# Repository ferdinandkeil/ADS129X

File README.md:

# ADS129X

Driver and sketches for the Texas Instruments **ADS1299-4 / ADS1299-6 / ADS1299** on a **Teensy 3.6, 4.0, or 4.1**, plus a Classic-Bluetooth sketch for the **original ESP32** (ESP32-WROOM-32E or ESP32-PICO, for example the Adafruit ESP32 Feather V2).

The photographed carrier is a Teensy 4.0 stacked on an **ADS1299-6**. The firmware reads the ID register and uses that channel count. If the ID does not look like an ADS1299, it assumes **6 channels**. Host output is still an **8-channel OpenBCI packet**; channels the chip does not have are zero.

This follows the ADS1299 datasheet (SBAS499C), not the ADS1298 ECG defaults. There is no respiration, pace, or Wilson-terminal register. Address `0x15` is `MISC1` (SRB1). Bias is `BIAS_SENSP` / `BIAS_SENSN`.

## Wiring

SPI is **mode 1** (CPOL = 0, CPHA = 1), MSB first. SCLK is requested at **8 MHz** (the part allows 20 MHz at DVDD >= 2.7 V). `MOSI` drives ADS1299 `DIN`. `MISO` reads `DOUT`.

Tie `CLKSEL` high for the internal 2.048 MHz oscillator, and tie `DAISY_IN` to DGND when this is the only device. `PWDN` and `RESET` are active low. Hold `START` low until the sketch starts conversions. DRDY falls when a new frame is ready; the interrupt is falling-edge.

Analog supplies, the bias resistor network, and SRB1/BIASOUT wiring are on the carrier. The firmware turns the internal 4.5 V reference and the bias amplifier on; it does not create that analog network.

### Teensy 3.6, 4.0, and 4.1

These pins are the same on all three boards and match the stacked carrier used by `Serial_OBCI` (DRDY on 2, PWDN on 3, RESET on 5, START on 6, CS on 10). An earlier loose prototype used a different map (PWDN 2, RESET 3, START 4, DRDY 5, CS 10). Confirm the silk before flashing that older board. Override a pin with `-DADS1299_PIN_DRDY=5` (and the matching `ADS1299_PIN_*` names) or by editing the defaults in `ADS129X.h`.

| Teensy pin | ADS1299 pin | Notes |
| --- | --- | --- |
| 13 (SCK) | SCLK | Hardware SPI. Do not use the onboard LED; it shares this pin. |
| 11 (MOSI) | DIN | |
| 12 (MISO) | DOUT | |
| 10 | CS | Active low, GPIO, not the SPI peripheral's automatic CS. |
| 2 | DRDY | Falling-edge interrupt. |
| 6 | START | Held low during setup, then driven high. |
| 5 | RESET | Active low. Pulsed after the power-up wait. |
| 3 | PWDN | Active low. Driven high to run. |
| GND | DGND, AGND | Common ground. |
| 3.3 V | DVDD | Logic supply. AVDD / AVSS stay on the carrier. |

### Adafruit ESP32 Feather V2 (original ESP32)

This is **not** the stacked Teensy carrier. It is a suggested jumper map for a Feather V2 or any original ESP32 module using these GPIO numbers. ESP32-S2, S3, C3, and C6 are refused: they do not have Bluetooth Classic SPP.

Do not use a DevKit's default VSPI labels (SCK 18, MOSI 23) with this sketch. Wire the GPIOs below. GPIO 34 is input-only and has no internal pull-up; the ADS1299 drives DRDY.

| Feather V2 pin | GPIO | ADS1299 pin |
| --- | --- | --- |
| SCK | 5 | SCLK |
| MO | 19 | DIN |
| MI | 21 | DOUT |
| 33 | 33 | CS |
| A2 | 34 | DRDY |
| 27 | 27 | START |
| A1 | 25 | RESET |
| A0 | 26 | PWDN |
| GND | GND | DGND / AGND |

## What the chip setup does

1. Drive `PWDN` high and hold `RESET` low, then wait 150 ms (`tPOR` is 128 ms at 2.048 MHz; the datasheet's typical power-up is 150 ms).
2. Release `RESET` and wait 18 `tCLK` (~9 µs). The reset low time is longer than the 2 `tCLK` minimum.
3. Send `SDATAC` before any register access. The part wakes in `RDATAC`, and register reads and writes are ignored until `SDATAC`.
4. Read `ID`. `NU_CH` `00` / `01` / `10` means 4 / 6 / 8 channels. Production IDs are usually `0x3C`, `0x3D`, and `0x3E`.
5. `CONFIG1` keeps the reserved bits set (`0x90 | DR`). Data rates are 250 SPS through 16 kSPS. `111` is not used.
6. `CONFIG3` sets bit 7 so the internal reference buffer is on (`0xE0` plus bias bits). The reference start-up wait is 150 ms.
7. Referential sketches close SRB1 (`MISC1 = 0x20`) and put every present channel into `BIAS_SENSP` and `BIAS_SENSN`.
8. `RDATAC`, then the `START` pin goes high. Samples are read on DRDY falling.
9. A frame is 3 status bytes plus 3 bytes per real channel (27 / 21 / 15). Channel data is 24-bit two's complement, sign-extended to 32 bits in `getData()`. Status bits `[23:20]` should read `1100`.

## OpenBCI packets

`Serial_OBCI`, `Serial_EMG`, and `ESP32_SPP` wait for `b` and then write the [Cyton 33-byte frame](https://docs.openbci.com/Cyton/CytonDataFormat/):

| Bytes | Contents |
| --- | --- |
| 0 | `0xA0` |
| 1 | Sample number, 0–255, wrapping |
| 2–25 | Eight 24-bit signed channel values, MSB first |
| 26–31 | Zeros (no accelerometer, so this is not live accel data) |
| 32 | `0xC0` |

The GUI's default scale is `µV = count * (4.5 / 8388607 / gain) * 1e6` with gain 24. `Serial_OBCI` and `ESP32_SPP` use that gain and 250 SPS. `Serial_EMG` uses gain 12 and 2 kSPS, so change the GUI scale before trusting its microvolt axis.

Startup text ends with `$$$`. Commands that answer do so only while streaming is off, so a reply cannot land in the middle of a binary packet.

| Command | Effect |
| --- | --- |
| `b` / `s` | Start or stop the binary stream |
| `v` | Reset the ADS1299, rewrite registers, print the banner |
| `V` | Print `ADS129X-2.0.0$$$` |
| `?` | Read back registers `0x00`–`0x17` |
| `xCHPDGAININBIASSRB2SRB1X` | One channel, same character codes as the Cyton SDK |
| `1`–`8` and `!@#$%^&*` | Power a channel down or up. Powered-down inputs are shorted, and the packet channel is zero |
| `d` / `D` | Restore or report the sketch's default channel template |
| `~0` … `~6` or `~~` | Set or query the data rate (`0` = 16 kSPS … `6` = 250 SPS) |

`z...Z` lead-off commands are consumed so the parser stays aligned, and answered with `not implemented`. Daisy-chain, SD logging, and real accelerometer bytes are not implemented.

## Sketches

| Sketch | Board | Output |
| --- | --- | --- |
| `examples/Serial_OBCI` | Teensy | OpenBCI packets. Referential EEG, gain 24, 250 SPS, SRB1 closed, bias on. |
| `examples/Serial_EMG` | Teensy | OpenBCI packets. Differential inputs, gain 12, 2 kSPS, SRB1 open, bias on. |
| `examples/Serial_Plotter` | Teensy | Eight signed counts, space-separated, for the Arduino Serial Plotter. Same analog setup as `Serial_OBCI`. Starts on its own. |
| `examples/Test_Signal` | Teensy | Same text format. Internal ~2 Hz square wave, gain 1. Expect about ±3495 counts (`VREF/2400` into gain 1). |
| `examples/ESP32_SPP` | Original ESP32 | Same EEG setup as `Serial_OBCI`. Packets on USB serial and Bluetooth SPP name `ADS1299-EEG`. Feather V2 pin map. |
| `examples/ESP32_OpenBCI` | ESP32 and ESP32-S3 dev modules | Same EEG setup, plus WiFi (OpenBCI WiFi Shield HTTP/TCP/UDP) and Bluetooth. See below. |

The first conversions after `START` are sinc-filter settling (about 16 ms at 250 SPS). Status is not a plotter column; `getData()` still returns it in `sample[0]`.

## ESP32 WiFi and Bluetooth

`examples/ESP32_OpenBCI` is the dev-board sketch. It is not the Feather map in `ESP32_SPP`. SPI pins are the Arduino defaults for **ESP32 Dev Module** and **ESP32-S3 Dev Module**, and each one is a `#define` (`ADS_PIN_SCLK`, `ADS_PIN_MISO`, `ADS_PIN_MOSI`, `ADS_PIN_CS`, `ADS_PIN_DRDY`, `ADS_PIN_START`, `ADS_PIN_RESET`, `ADS_PIN_PWDN`) so a different board is a build flag or a one-line edit.

| ADS1299 | ESP32 Dev Module | ESP32-S3 Dev Module |
| --- | --- | --- |
| SCLK | 18 | 12 |
| DIN (MOSI) | 23 | 11 |
| DOUT (MISO) | 19 | 13 |
| CS | 5 | 10 |
| DRDY | 27 | 4 |
| START | 25 | 5 |
| RESET | 26 | 6 |
| PWDN | 32 | 7 |

Leave `STA_SSID` empty and the board starts an access point named `ADS1299-EEG`, password `openbci123`, at **192.168.4.1**. Set `STA_SSID` / `STA_PASSWORD` to join a router instead; if that join fails, it falls back to the same access point. The serial monitor prints the IP. HTTP is port 80.

DRDY is still the sample clock. On ESP32 the GPIO interrupt only wakes a high-priority task (the Arduino SPI driver cannot be called from that interrupt). That task clocks the frame and pushes a 33-byte packet into a 512-deep ring. `loop()` drains the ring onto WiFi and Bluetooth, so a stalled `write` does not have to finish before the next SPI read. `ringDropped()` counts packets that did not fit. The USB line `# ring_dropped=` is printed while USB itself is not streaming binary.

WiFi matches the OpenBCI WiFi Shield enough for BrainFlow and the GUI:

| Request | Role |
| --- | --- |
| `GET /board` | `{"board_connected","board_type":"cyton","num_channels":8,"gains":[...]}` |
| `POST /tcp` | JSON `ip`, `port`, `output` (`raw` or `json`), `delimiter`, `latency`. The ESP32 connects **to that computer** and, once streaming, writes samples. |
| `POST /udp` | Same JSON. One datagram per sample. `"redundancy":true` sends it three times. |
| `POST /command` | `{"command":"~4"}` and the other Cyton ASCII commands. |
| `GET /stream/start` | Starts conversions (`b`). |
| `GET /stream/stop` | Stops them when no other transport still wants samples. |

`raw` output is concatenated 33-byte packets (`0xA0` … `0xC0`). `json` output is one `{"chunk":[{"data":[nanovolts...],"timestamp":...}]}` object per sample, with `\r\n` when `delimiter` is true. BrainFlow asks for `raw`. The `latency` value is accepted and reported; packets are sent on the next `loop()` pass rather than held for that many microseconds.

BrainFlow (the computer listens, the board calls out):

```python
from brainflow.board_shim import BoardShim, BrainFlowInputParams, BoardIds

params = BrainFlowInputParams()
params.ip_address = "192.168.4.1"  # or the STA address printed at boot
params.ip_port = 6677              # free port on this computer
board = BoardShim(BoardIds.CYTON_WIFI_BOARD, params)
board.prepare_session()            # GET /board, POST /tcp, then ~4 (1000 SPS)
board.start_stream()               # GET /stream/start
```

In the OpenBCI GUI choose Cyton over WiFi and enter that IP. `prepare_session` always sends `~4`, so a BrainFlow session runs at **1000 SPS** even though the sketch boots at 250.

Classic Bluetooth SPP is compiled only for the original ESP32 (the S3 has no Classic radio). Pair with `ADS1299-EEG`. The port is a normal serial port: GUI "Cyton (live from serial / dongle)", or BrainFlow `BoardIds.CYTON_BOARD` with `params.serial_port`. Send `b` / `s` as usual.

ESP32-S3 uses BLE Nordic UART under the same name (`6E400001-B5A3-F4F5-A9E5-9E4000000000`). Notifications are 20 bytes so they fit the default ATT MTU; a client has to concatenate them back into 33-byte packets. The OpenBCI GUI does not open a Cyton over BLE. A BLE serial app can send `b` and read the stream.

These rates are from the 33-byte packet and typical radio throughput. They were not measured on hardware.

| Transport | Rate that should fit | Notes |
| --- | --- | --- |
| USB serial at 115200 | 250 SPS | About 11 KB/s on the wire. |
| Classic SPP | 250 SPS, often 1000 | 1000 SPS is 33 KB/s. 2000 SPS is optimistic. |
| BLE notifications | 250 SPS | Two notifications per packet at the default MTU. |
| WiFi TCP | 250 through about 4–8 kSPS | 8 kSPS is about 264 KB/s. 16 kSPS is about 528 KB/s, and the ring is only 32 ms deep at that rate. |
| WiFi UDP | Same order as TCP | Loss is visible as sample-number gaps. Redundancy multiplies the airtime. |

The 512-packet ring is about 2 s at 250 SPS and about 0.5 s at 1000 SPS.

## Build

Install [arduino-cli](https://arduino.github.io/arduino-cli/), then the cores:

```bash
arduino-cli config init
arduino-cli config add board_manager.additional_urls https://www.pjrc.com/teensy/package_teensy_index.json
arduino-cli config add board_manager.additional_urls https://espressif.github.io/arduino-esp32/package_esp32_index.json
arduino-cli core update-index
arduino-cli core install teensy:avr
arduino-cli core install esp32:esp32
```

From a checkout of this repository (the folder that contains `ADS129X.h`):

```bash
mkdir -p /tmp/ardulibs
ln -sfn "$PWD" /tmp/ardulibs/ADS129X

arduino-cli compile --fqbn teensy:avr:teensy40 --libraries /tmp/ardulibs examples/Serial_OBCI
arduino-cli compile --fqbn teensy:avr:teensy41 --libraries /tmp/ardulibs examples/Serial_OBCI
arduino-cli compile --fqbn teensy:avr:teensy36 --libraries /tmp/ardulibs examples/Serial_OBCI

arduino-cli compile --fqbn teensy:avr:teensy40 --libraries /tmp/ardulibs examples/Serial_EMG
arduino-cli compile --fqbn teensy:avr:teensy40 --libraries /tmp/ardulibs examples/Serial_Plotter
arduino-cli compile --fqbn teensy:avr:teensy40 --libraries /tmp/ardulibs examples/Test_Signal

arduino-cli compile --fqbn esp32:esp32:adafruit_feather_esp32_v2 --libraries /tmp/ardulibs examples/ESP32_SPP

# Default 1.2 MB app partition is too small for WiFi + Bluetooth.
# Huge APP is 3 MB and has no OTA slot. Minimal SPIFFS (1.9 MB) also fits.
arduino-cli compile --fqbn esp32:esp32:esp32:PartitionScheme=huge_app --libraries /tmp/ardulibs examples/ESP32_OpenBCI
arduino-cli compile --fqbn esp32:esp32:esp32s3:PartitionScheme=huge_app --libraries /tmp/ardulibs examples/ESP32_OpenBCI
```

In the Arduino IDE, install **Teensy (for Arduino IDE 2.x)** and **esp32** by Espressif, then open a sketch from `examples/`. Pick Teensy 4.0, 4.1, or 3.6, **Adafruit Feather ESP32 V2** for `ESP32_SPP`, or **ESP32 Dev Module** / **ESP32S3 Dev Module** for `ESP32_OpenBCI`. For that last sketch set **Tools → Partition Scheme → Huge APP (3MB No OTA/1MB SPIFFS)**. USB serial on the Feather and on Dev Modules is 115200. Teensy USB serial ignores the baud number.

`examples/ESP32_SPP` does not compile for ESP32-S2/S3/C3/C6 on purpose. `examples/ESP32_OpenBCI` compiles for the original ESP32 and the ESP32-S3.

Checked with arduino-cli, Teensy core 1.62.0, and ESP32 core 3.3.12. No ADS1299 was attached.

| Sketch | Teensy 4.0 | Teensy 4.1 | Teensy 3.6 | Feather ESP32 V2 | ESP32 Dev Module | ESP32-S3 Dev Module |
| --- | --- | --- | --- | --- | --- | --- |
| Serial_OBCI | yes | yes | yes | | | |
| Serial_EMG | yes | yes | yes | | | |
| Serial_Plotter | yes | yes | yes | | | |
| Test_Signal | yes | yes | yes | | | |
| ESP32_SPP | | | | yes | yes | |
| ESP32_OpenBCI | | | | | yes (Huge APP) | yes (Huge APP) |

The same four Teensy sketches also compiled for Teensy 3.2 / 3.1 (`teensy:avr:teensy31`). Adafruit Feather ESP32-S3 stops in `ESP32_SPP` with the Classic-Bluetooth error. A Dev Module build of `ESP32_SPP` still uses the Feather GPIO numbers in the wiring table above. `ESP32_OpenBCI` on a Dev Module uses the dev-board pins in the ESP32 section.

Nothing in this tree was run on the carrier. Confirm the ID line (`0x3D` for an ADS1299-6), that status bits `[23:20]` are `1100`, and that the test-signal sketch steps by about ±3495 counts before trusting electrode data.

## Hardware

Board designs live in [`hardware/`](hardware). [`hardware/README.md`](hardware/README.md) indexes them: the ESP32-DevKitC carrier, and the XIAO boards for the ADS1299, ADS1298 and AD7771, with their XIAO pin maps and open items.

## License

MIT. See [LICENSE.md](LICENSE.md). Original ADS1299 code by Conor Russomanno; the earlier Arduino port by Ferdinand Keil.

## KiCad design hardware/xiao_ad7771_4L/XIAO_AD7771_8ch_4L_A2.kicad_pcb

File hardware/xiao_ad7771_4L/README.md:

# XIAO-AD7771 8-channel shield, 4-layer, A1-4L

**Board**
- 20.0 × 25.8 mm, the same outline as the ADS1299 R2 board.
- The XIAO sockets and the 2×7 output header are in the same places as on R2.
- OSH Park 4-layer: about 0.80 sq in, so roughly $8 for three boards.

**Design rules**
- DRC is clean, apart from one cosmetic note: the C13 label touches a solder-mask opening.
- Clearance 0.13 mm.
- Traces 0.13–0.25 mm.
- Vias 0.5/0.254 mm.
- Minimum silkscreen text 0.6 mm.
- These are within OSH Park's 4-layer rules (5/5 mil, 10 mil drill).

**Input protection:** there are no input protection resistors on this board. Whatever plugs into J3 must carry them, for example 2.2 kΩ in series with each electrode. The AD7771 inputs are only rated −0.3 V to 3.6 V.

## Layer stack

| Layer | Use |
|---|---|
| F (XIAO side) | AVDD pour behind the chip, ground pour, a few digital lines, guard pour over the output end, SRB link |
| In1 | Solid ground plane |
| In2 | The eight input traces, run inside a guard pour from the chip to the header, with a ground island under the chip |
| B (chip side) | AD7771, op-amp block, passives, digital fan-out, guard around the SRB buses and the header |

The input traces never run on an outer layer. From each AINx+ pin they drop straight into In2 through a via, cross under the chip and come up at the header. On In2 the guard pour surrounds them.

## Circuit

The circuit is the same as the 2-layer A1, with these differences:

- **Op-amp sections:** U2 is still an OPA2333, but the sections are swapped.
  - **B is the bias integrator:** +INB = AD7771 VCM, −INB = BIASINV, OUTB → R2 (100 kΩ) → BIASOUT.
  - **A is the guard buffer:** +INA = SRB, OUTA → R3 (4.7 kΩ) → GUARD.
  - As on A1, R1 (1 MΩ) runs from the buffered SRB to BIASINV, and C13 is 270 pF C0G. Crossover is about 590 Hz and bias current is at most about 16 µA.
- **Op-amp supply:** U2 gets AVDD through a short inner-layer link inside the ground island.
- **No status LED:** there was no room left for it on this size. AD7771 GPIO0 is unconnected.
- **No local op-amp bypass cap:** there is no dedicated 100 nF beside U2. It is fed from the AVDD pour, with C6 about 6 mm away. That is fine for an op-amp drawing 17 µA.
- **Reference:** internal 2.5 V. REF_OUT is decoupled with C8. REF1± and REF2± are tied to ground. Firmware must select the internal reference (ADC_MUX_CONFIG REF_MUX_CTRL = 01) and enable the internal reference buffer.
- **Clock:** CLK_SEL is low, so the clock comes from XIAO D10 through R7 (47 Ω). Y1 (DNP, top side) plus JP3 is the optional oscillator.

## Output header J3 (2×7): same pinout as R2 and A1

| Column | Inner row | Outer row |
|---|---|---|
| 1 | 1 IN1 (AIN1) | 2 IN2 (AIN0) |
| 2 | 3 IN3 (AIN3) | 4 IN4 (AIN2) |
| 3 | 5 IN5 (AIN7) | 6 IN6 (AIN6) |
| 4 | 7 IN7 (AIN5) | 8 IN8 (AIN4) |
| 5 | 9 SRB | 10 NC |
| 6 | 11 BIASOUT | 12 GUARD |
| 7 | 13 BIASINV | 14 GUARD |

- **Channel order:** the order on the inner layer keeps both input fans free of crossings. Reorder in firmware: `IN = [1, 0, 3, 2, 7, 6, 5, 4]`. Note that this differs from the 2-layer A1.

## XIAO pins (different from A1, chosen for this layout)

| XIAO pin | ESP32-S3 GPIO | Signal |
|---|---|---|
| D0 | GPIO1 | MISO (SDO) |
| D1 | GPIO2 | MOSI (SDI) |
| D2 | GPIO3 | SCK |
| D3 | GPIO4 | CS, board 1 (JP1 to D3) |
| D4 | GPIO5 | CS, board 2 (JP1 to D4) |
| D10 | GPIO9 | MCLK, 8 MHz LEDC (shared by a stack) |
| D9 | GPIO8 | DRDY (JP2) |
| D8 | GPIO7 | RESET (shared) |

- **Free:** D5, D6 and D7.

## Solder jumpers (all ship open)

| Jumper | Side | Silkscreen | Bridge | Effect |
|---|---|---|---|---|
| JP1 | bottom | D3 / CS / D4 | centre to D3 | CS on D3 (single board or board 1) |
| | | | centre to D4 | CS on D4 (board 2) |
| JP2 | bottom | DRDY | bridge | DRDY to D9 (board 1 or a single board only) |
| JP3 | top | OSC | bridge | Y1 onto MCLK (only with Y1 fitted; keep XIAO D10 as an input) |

## Two boards in a stack

- **Board 2:** JP1 to D4, JP2 open, and leave off R1, R2 and C13.
- **Wiring:** link pins 13 and 14 between the boards, and wire both SRB pins to the same electrode.
- **Starting both boards together:** pull both CS lines low and issue SPI_SYNC.

## Assembly

- **Bottom side:** U1, U2, the jumpers and all other passives.
- **Top side:** C4, C5, C6, C9 and C11 (100 nF, right behind U1), plus the optional Y1 and JP3.
  - That makes JLC assembly two-sided. Or hand-solder the five caps after reflow.
- **Files:** use `_BOM_JLC.csv` and `_CPL_JLC.csv`.

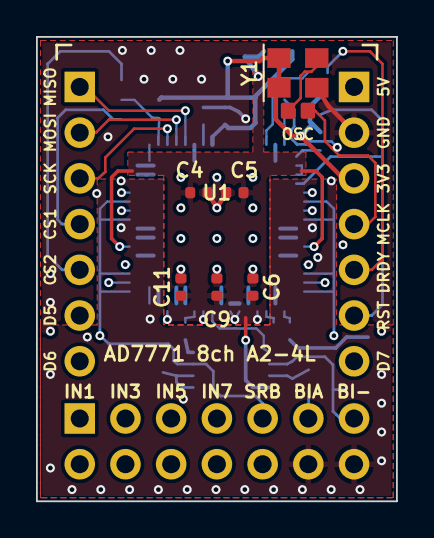
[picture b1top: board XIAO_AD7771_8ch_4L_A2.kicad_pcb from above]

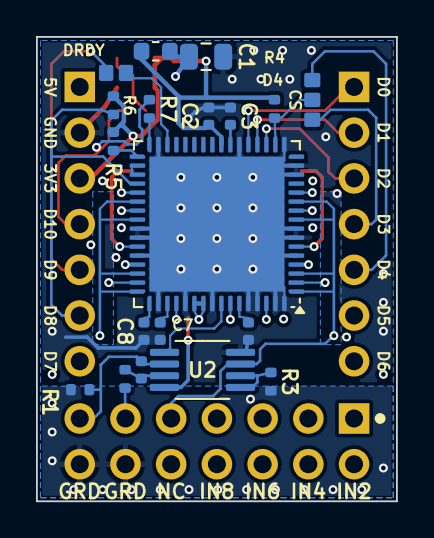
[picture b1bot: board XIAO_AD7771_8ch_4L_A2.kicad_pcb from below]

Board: 4 copper layers, 20.0 x 25.8 mm, 29 parts (20 on the bottom side), 36 nets.

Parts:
C1: 10u; C_0805_2012Metric
C2, C4, C5, C6, C8, C9, C11: 100n; C_0402_1005Metric
C3, C7, C10: 1u; C_0402_1005Metric
C13: 270p C0G; C_0402_1005Metric
FB1: 600R@100M; L_0603_1608Metric
J1: XIAO D0-D6; PinHeader_1x07_P2.54mm_Vertical
J2: XIAO 5V..D7; PinHeader_1x07_P2.54mm_Vertical
J3: Out 2x7 RA; PinHeader_2x07_P2.54mm_Horizontal
JP1: CS D1/D3; SJ3
JP2: DRDY; SJ2
JP3: OSC; SJ2
R1: 1M; R_0402_1005Metric
R2: 100k; R_0402_1005Metric
R3: 4.7k; R_0402_1005Metric
R4, R5, R6: 10k; R_0402_1005Metric
R7: 47; R_0402_1005Metric
U1: AD7771BCPZ; QFN-64-1EP_9x9mm_P0.5mm_EP7.5x7.5mm
U2: OPA2333AIDGKR; MSOP-8_3x3mm_P0.65mm
Y1: 8MHz DNP; Oscillator_SMD_Abracon_ASE-4Pin_3.2x2.5mm

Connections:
3V3: C2.2, FB1.2, J2.3, R4.1, R5.1, R6.1, U1.24, Y1.1, Y1.4
AREG1: C10.1, U1.59
AREG2: C7.1, U1.51
AVDD: C1.2, C4.1, C5.1, C6.2, C9.2, C11.2, FB1.1, U1.6, U1.43, U1.52, U1.54, U1.55, U1.58, U1.62, U2.8
BIASINV: C13.1, J3.13, R1.1, U2.6
BIASOUT: J3.11, R2.2
BIAS_O: C13.2, R2.1, U2.7
CS: JP1.2, R4.2, U1.18
CS1: J1.4, JP1.1
CS2: J1.5, JP1.3
DRDY: JP2.1, U1.30
DRDYX: J2.5, JP2.2
DREG: C3.2, U1.23
GBUF: R3.1, U2.1, U2.2
GND: C1.1, C2.1, C3.1, C4.2, C5.2, C6.1, C7.2, C8.2, C9.1, C10.2, C11.1, J2.2, U1.5, U1.7, U1.8, U1.14, U1.15, U1.17, U1.22, U1.31, U1.41, U1.42, U1.44, U1.50, U1.53, U1.56, U1.60, U1.61, U1.63, U1.64, U1.65, U2.4, Y1.2
GUARD: J3.12, J3.14, R1.2, R3.2
IN1: J3.1, U1.4
IN2: J3.2, U1.2
IN3: J3.3, U1.10
IN4: J3.4, U1.12
IN5: J3.5, U1.37
IN6: J3.6, U1.39
IN7: J3.7, U1.45
IN8: J3.8, U1.47
MCLK: J2.4, JP3.2, R7.1
MCLK_U: R7.2, U1.32
MISO: J1.1, U1.21
MOSI: J1.2, U1.20
OSC: JP3.1, Y1.3
REF: C8.1, U1.49
RESET: J2.6, R6.2, U1.36
SCK: J1.3, U1.19
SRB: J3.9, U1.1, U1.3, U1.9, U1.11, U1.38, U1.40, U1.46, U1.48, U2.3
START: R5.2, U1.33
SYNC: U1.34, U1.35
VCM: U1.57, U2.5

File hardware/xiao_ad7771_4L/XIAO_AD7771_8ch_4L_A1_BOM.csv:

Refs,Qty,Value / part,Footprint,Side,Note
C1,1,10u,C_0805_2012Metric,Bottom (chip side),
C2 C8,2,100n,C_0402_1005Metric,Bottom (chip side),
C3 C7 C10,3,1u,C_0402_1005Metric,Bottom (chip side),
C4 C5 C6 C9 C11,5,100n,C_0402_1005Metric,Top (XIAO side),"Top side, behind U1"
C13,1,270p C0G,C_0402_1005Metric,Bottom (chip side),C0G/NP0. Omit on the 2nd board of a stack
FB1,1,600R@100M,L_0603_1608Metric,Bottom (chip side),e.g. Murata BLM18KG601SN1D
J1,1,XIAO D0-D6,PinHeader_1x07_P2.54mm_Vertical,Top (XIAO side),XIAO socket or pins
J2,1,XIAO 5V..D7,PinHeader_1x07_P2.54mm_Vertical,Top (XIAO side),XIAO socket or pins
J3,1,Out 2x7 RA,PinHeader_2x07_P2.54mm_Horizontal,Bottom (chip side),2x7 right-angle header (or 2x6 + 1x2)
R1,1,1M,R_0402_1005Metric,Bottom (chip side),Omit on the 2nd board of a stack
R2,1,100k,R_0402_1005Metric,Bottom (chip side),Bias output current limit. Omit on the 2nd board of a stack
R3,1,4.7k,R_0402_1005Metric,Bottom (chip side),
R4 R5 R6,3,10k,R_0402_1005Metric,Bottom (chip side),
R7,1,47,R_0402_1005Metric,Bottom (chip side),
U1,1,AD7771BCPZ,QFN-64-1EP_9x9mm_P0.5mm_EP7.5x7.5mm,Bottom (chip side),"AD7771BCPZ (LFCSP-64 9x9). Analog Devices, US distributors: Digi-Key, Mouser"
U2,1,OPA2333AIDGKR,MSOP-8_3x3mm_P0.65mm,Bottom (chip side),"OPA2333AIDGKR (dual, zero-drift). B = bias integrator, A = guard buffer"
Y1,1,8MHz DNP,Oscillator_SMD_Abracon_ASE-4Pin_3.2x2.5mm,Top (XIAO side),"DNP. Optional 3.3 V CMOS oscillator (e.g. 8.192 MHz, 3.2x2.5 mm), top side; enable with JP3"

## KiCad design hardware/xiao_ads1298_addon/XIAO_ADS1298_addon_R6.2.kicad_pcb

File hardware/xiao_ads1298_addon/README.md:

# XIAO ADS1298 add-on, R6.2 (18-pin flex inputs)

**R6.2** is the 18-pin flex board with every via moved off component pads. Earlier revisions: R6. Parts and placement are unchanged. **One pinout change:** the ADS clock between stacked boards moved from D6 to D1, and the silkscreen is relabelled to match. Main and add-on boards of the same revision must be used together.

## R6.2 changes: vias off pads
A via on or touching a small pad can wick solder away from the joint. On 0.5 mm-pitch pins its ring can also bridge to the next pin.

- **New positions:** each via now sits beside its pad, joined by a short straight or 45° trace.
- **Re-joined traces:** traces that met the via are re-routed from their previous corner, straight and at 45°.
- **Checks:** the design-rule report matches the original board's line for line, nothing is unconnected, and `tools/check_via_in_pad.py` finds no via in any part pad.
- **"Drill clear" rows** in the table: the hole is off the pad and the ring still touches the pad edge. Vias are tented, so no solder reaches the hole.
- **U1 pin 62 (AVDD):** the via sits just past the pin tip with its drill clear. The ring still touches the tip, because neighbouring traces leave no room further out. Its top-side trace to the decoupling cap is rerouted at 45°, where it used to run at an angle.

| Pad | Net | Via moved | Distance | Result |
|---|---|---|---|---|
| U1.62 | AVDD | (4.85, 2.75) → (4.75, 2.75) | 0.10 mm | drill clear |
| C4.2 | GND | (-1.60, -1.60) → (-0.69, -2.02) | 1.00 mm | clear |
| C3.2 | GND | (-2.40, 0.40) → (-2.11, 0.06) | 0.45 mm | clear |
| C5.2 | GND | (-3.00, -3.60) → (-2.92, -3.47) | 0.15 mm | clear |
| C9.2 | GND | (2.60, -4.20) → (1.92, -4.38) | 0.70 mm | clear |
| C8.2 | GND | (2.20, -3.20) → (1.89, -2.75) | 0.55 mm | clear |
| C5.1 | VCAP2 | (-4.65, -4.93) → (-4.49, -5.12) | 0.25 mm | clear |
| C9.1 | DVDD | (3.60, -4.20) → (3.52, -3.91) | 0.30 mm | clear |

`plots/*_via_check.png` shows pads and vias, before and after.

## XIAO nRF54L15

The XIAO pins match every XIAO, including the nRF54L15, and SPI sits on that board's high-speed SPI:

| XIAO pin | nRF54L15 | Use here |
|---|---|---|
| D8 / D9 / D10 | P2.01 / P2.04 / P2.02 | SCK / MISO / MOSI on **SPIM00** (Zephyr `xiao_spi` = `&spi00`) |
| D0 | P1.04 | DRDY (main). P1 supports pin interrupts; P2 GPIOs don't |
| D3 | P1.07 | CS (main) |
| D7 | P2.07 | CS2 (add-on) |
| D4 / D5 | P1.10 / P1.11 | I²C (`i2c22`), main board only |
| D1 | P1.05 | ADS clock pass-through between stacked boards (moved from D6 in this revision) |

- **D6 is free now.** The clock used to share D6 with the UART TX that Zephyr enables by default (`uart21`), so it moved to D1. With an add-on fitted, D7 is CS2, so disable `uart21` then: `&uart21 { status = "disabled"; };`.
- **USB power only:** AVDD comes from the XIAO 5 V pin through FB1, and that pin carries no usable 5 V when the XIAO runs on battery alone.

## Inputs, aux header and guard
See [`../FLEX18.md`](../FLEX18.md): 18-pin Hirose FH12 flex input, 2×3 1.27 mm aux header, and closed guard on all four layers.

## Files
| File | Contents |
|---|---|
| `XIAO_ADS1298_addon_R6.2.kicad_pcb` / `.kicad_pro` | KiCad 7 board and rules |
| `gerber/` | Gerbers and drill file (4 layers) |
| `XIAO_ADS1298_addon_R6.2_BOM.csv` | Bill of materials |
| `plots/` | Top/bottom view, copper by net, via check |

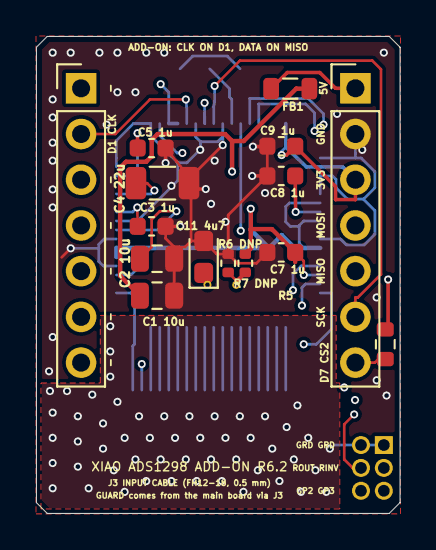
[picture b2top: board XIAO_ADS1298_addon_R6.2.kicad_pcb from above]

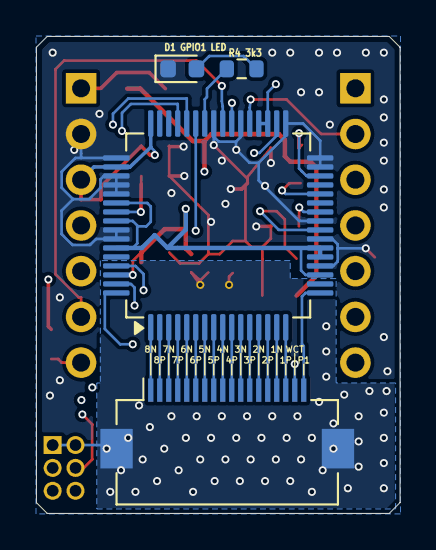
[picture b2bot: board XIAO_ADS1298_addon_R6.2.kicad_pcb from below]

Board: 4 copper layers, 20.2 x 26.5 mm, 22 parts (5 on the bottom side), 39 nets.

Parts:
C1, C2: 10u; C_0805_2012Metric
C3, C5, C7, C8, C9: 1u; C_0603_1608Metric
C4: 22uF 6.3V; C_1206_3216Metric
C11: 4.7u 10V tant; CP_EIA-2012-12_Kemet-R
D1: LED; LED_0603_1608Metric
FB1: 600R@100MHz; L_0805_2012Metric
GV1, GV2: guard via; GuardVia
J1: XIAO left (pass-through); PinHeader_1x07_P2.54mm_Vertical
J2: XIAO right (pass-through); PinHeader_1x07_P2.54mm_Vertical
J3: FH12-18S-0.5SH(55); Hirose_FH12-18S-0.5SH_1x18-1MP_P0.50mm_Horizontal
J4: 2x3 1.27mm; PinHeader_2x03_P1.27mm_Vertical
R4: 3.3k; R_0603_1608Metric
R5: 10k; R_0603_1608Metric
R6, R7: 200k; R_0402_1005Metric
U1: ADS1298IPAG; TQFP-64_10x10mm_P0.5mm

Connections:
+5V: FB1.1, J2.1
AVDD: C1.1, C7.1, FB1.2, R6.2, U1.19, U1.21, U1.22, U1.54, U1.56, U1.59, U1.62
CLK: J1.2, U1.37
CS2: J2.7, R5.2, U1.39
DVDD: C9.1, J2.3, R5.1, U1.35, U1.36, U1.48, U1.50
GND: C1.2, C2.2, C3.2, C4.2, C5.2, C7.2, C8.2, C9.2, C11.2, D1.1, J2.2, R7.2, U1.20, U1.23, U1.25, U1.31, U1.32, U1.33, U1.38, U1.41, U1.49, U1.51, U1.52, U1.53, U1.57, U1.58
GPIO1: R4.1, U1.42
GPIO2: J4.6, U1.44
GPIO3: J4.5, U1.45
GUARD: C11.1, GV1.1, GV2.1, J3.MP, J4.1, J4.2, R6.1, R7.1
IN1N: J3.15, U1.15
IN1P: J3.16, U1.16
IN2N: J3.13, U1.13
IN2P: J3.14, U1.14
IN3N: J3.11, U1.11
IN3P: J3.12, U1.12
IN4N: J3.9, U1.9
IN4P: J3.10, U1.10
IN5N: J3.7, U1.7
IN5P: J3.8, U1.8
IN6N: J3.5, U1.5
IN6P: J3.6, U1.6
IN7N: J3.3, U1.3
IN7P: J3.4, U1.4
IN8N: J3.1, U1.1
IN8P: J3.2, U1.2
LED_A: D1.2, R4.2
MISO: J2.5, U1.43
MOSI: J2.4, U1.34
PACE1: J3.18, U1.17
RLDINV: J4.3, U1.61
RLDOUT: J4.4, U1.63
SCK: J2.6, U1.40
VCAP1: C4.1, U1.28
VCAP2: C5.1, U1.30
VCAP3: C8.1, U1.55
VCAP4: C3.1, U1.26
VREFP: C2.1, U1.24
WCT: J3.17, U1.64

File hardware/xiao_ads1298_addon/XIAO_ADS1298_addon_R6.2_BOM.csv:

Refs,Qty,Value / part,Footprint,Side
C1 C2,2,10u,C_0805_2012Metric,Top
C3 C5 C7 C8 C9,5,1u,C_0603_1608Metric,Top
C4,1,22uF 6.3V,C_1206_3216Metric,Top
C11,1,4.7u 10V tant,CP_EIA-2012-12_Kemet-R,Top
D1,1,LED,LED_0603_1608Metric,Bottom
FB1,1,600R@100MHz,L_0805_2012Metric,Top
J1,1,XIAO left (pass-through),PinHeader_1x07_P2.54mm_Vertical,Top
J2,1,XIAO right (pass-through),PinHeader_1x07_P2.54mm_Vertical,Top
J3,1,FH12-18S-0.5SH(55),Hirose_FH12-18S-0.5SH_1x18-1MP_P0.50mm_Horizontal,Bottom
J4,1,2x3 1.27mm,PinHeader_2x03_P1.27mm_Vertical,Bottom
R4,1,3.3k,R_0603_1608Metric,Bottom
R5,1,10k,R_0603_1608Metric,Top
R6 R7,2,200k,R_0402_1005Metric,Top
U1,1,ADS1298IPAG,TQFP-64_10x10mm_P0.5mm,Bottom

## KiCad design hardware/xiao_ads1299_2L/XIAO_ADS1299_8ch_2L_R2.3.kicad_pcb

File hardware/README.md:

# Hardware index

Each folder holds one board line at its latest revision. Earlier revisions are in the Git history: `git log -- hardware/<folder>` lists them, and each commit message says what changed.

| Folder | Board | Chip | Layers | Latest | Inputs | Status |
|---|---|---|---|---|---|---|
| [`esp32_devkitc`](esp32_devkitc) | ESP32-DevKitC carrier | ADS1299 | 2 | (see its README) | electrode/5 V column | Not ready to fabricate |
| [`xiao_ads1299_main`](xiao_ads1299_main) | XIAO main board, 8 ch | ADS1299 | 4 | R5.2 (history: R5) | 18-pin 0.5 mm flex + 2×3 aux | Current |
| [`xiao_ads1299_addon`](xiao_ads1299_addon) | XIAO add-on, ch 9–16 | ADS1299 | 4 | R6.2 (history: R6) | 18-pin flex + 2×3 aux | Current |
| [`xiao_ads1298_main`](xiao_ads1298_main) | XIAO main board, 8 ch | ADS1298 | 4 | R5.2 (history: R5) | 18-pin flex, WCT on pin 17 | Current |
| [`xiao_ads1298_addon`](xiao_ads1298_addon) | XIAO add-on | ADS1298 | 4 | R6.2 (history: R6) | 18-pin flex | Current |
| [`lolin_ads1299`](lolin_ads1299) | LOLIN board, 8 ch | ADS1299 | 4 | R7.1 (history: R7) | 18-pin flex + 2×3 aux | Current |
| [`lolin_ads1298`](lolin_ads1298) | LOLIN board, 8 ch | ADS1298 | 4 | R7.1 (history: R7) | 18-pin flex + 2×3 aux | Current |
| [`xiao_ads1299_2L`](xiao_ads1299_2L) | XIAO shield, 8 ch, stackable | ADS1299 | 2 | R2.3 (history: R1, R2, R2.1, R2.2) | 2×7 right-angle 2.54 mm | Current |
| [`xiao_ad7771_4L`](xiao_ad7771_4L) | XIAO shield, 8 ch | AD7771 | 4 | A2 (history: A1) | 2×7 (R2 pinout) | Current |
| [`xiao_ad7771_2L`](xiao_ad7771_2L) | XIAO board, 8 ch | AD7771 | 2 | A1.2 (history: A1, A1.1) | 2×7 (R2 pinout) | Weak guard; rework only if needed |

The 18-pin flex, aux-header and guard design shared by the main, add-on and LOLIN boards is described in [`FLEX18.md`](FLEX18.md).

Every folder has the KiCad board (`.kicad_pcb`, `.kicad_pro`), its README, the BOM (and JLC BOM/CPL where made), `gerber/` and `plots/`.

**Not yet in this repository:** main board R1–R4 and add-on R5 of the 4-layer line, the touch-proof jack board (paused; must carry the input protection resistors), and any board still only on your drive. Add them with one commit per revision, oldest first.

## XIAO pin maps

| XIAO | nRF54L15 | ADS1299/1298 main R5.2 | Add-on R6.2 | ADS1299 2L R2.3 | AD7771 A1/A2-4L | AD7771 2L A1 |
|---|---|---|---|---|---|---|
| D0 | P1.04 | DRDY | — | DRDY (JP4) | MISO | MOSI |
| D1 | P1.05 | CLK pass-through | CLK pass-through | shared ADS clock (JP2) | MOSI | CS1 |
| D2 | P1.06 | PPG_INT | — | free | SCK | SCK |
| D3 | P1.07 | CS | — | CS1 (JP1) | CS1 | CS2 |
| D4 | P1.10 | SDA | — | free (I²C) | CS2 | MISO |
| D5 | P1.11 | SCL | — | free (I²C) | free | free |
| D6 | P2.08 | free | — | free | free | free |
| D7 | P2.07 | free | CS2 | CS2 (JP5) | free | MCLK |
| D8 | P2.01 | SCK | SCK | SCK | RESET | RESET |
| D9 | P2.04 | MISO | MISO | MISO | DRDY (JP2) | free |
| D10 | P2.02 | MOSI | MOSI | MOSI | MCLK | DRDY |

- **Main R5.2 / add-on R6.2:** standard XIAO SPI on D8–D10, so they work on the XIAO ESP32-S3, nRF52840 and nRF54L15. On the nRF54L15 these are SPIM00's fixed high-speed pins (P2.01/P2.04/P2.02), which ESP32 boards can map anywhere but the nRF54L15 can't. DRDY is on P1, which supports interrupts. The ADS clock passes between boards on D1 (P1.05), which has no default peripheral, so D6/D7 stay free for the XIAO UART. With an add-on fitted, D7 is CS2, so disable `uart21` then.
- **2-layer R2.3:** same pin map as main R5.2 / add-on R6.2: SPI on D8–D10 (SPIM00 on the nRF54L15), DRDY D0, clock D1, CS D3/D7. R2–R2.2 used D0/D2/D9 for SPI, which splits across nRF54L15 ports.
- **AD7771 4-layer:** on Nordic XIAOs, fit Y1, bridge JP3 and leave D10 as an input. The 8 MHz MCLK pin is on an nRF52840 low-frequency-only pin.
- **ESP32-C3:** D0, D8 and D9 are boot-strapping pins.

nRF54L15 pin names are from [Seeed's XIAO nRF54L15 wiki](https://wiki.seeedstudio.com/xiao_nrf54l15_sense_getting_started/). The AD7771 2L A1 map was reconstructed from notes; check it against its README.

## Shared output header on the 2×7 boards

R2–R2.3 and all AD7771 boards: pins 1–8 IN1–IN8, 9 SRB, 10 NC, 11 BIASOUT, 12 GUARD, 13 BIASINV, 14 GUARD. It carries no power or I2C; the sensor board takes those from the XIAO stack headers.

## Firmware channel remaps

| Board | `IN[]` |
|---|---|
| AD7771 A2-4L | `[1, 0, 2, 3, 7, 6, 5, 4]` |
| AD7771 A1-4L | `[1, 0, 3, 2, 7, 6, 5, 4]` |
| AD7771 2L A1 | `[2, 3, 0, 1, 4, 5, 6, 7]` |

## Checking for vias on pads

`tools/check_via_in_pad.py <board.kicad_pcb>` lists every via whose drill or ring touches a component pad, classed as exposed pad (expected), mounting tab, or part pad. Run it before ordering. KiCad's own design-rule check does not flag a via on a pad of the same net.

## Open items

- [ ] Check R2's SPI pins on the nRF54L15 with a Devicetree overlay, or revise R2 to use D8–D10.
- [ ] Measure the XIAO nRF54L15 stack's idle current when powered through USB (its SAMD11 programming chip stays on).
- [ ] Check AVDD at the ADS1299 under load when the 5 V comes from the boost converter (needs 4.75–5.25 V), and look for switching spurs.
- [ ] Consider the R2.1 guard filter (100 k + 2.2 µF) on the main R5.2 guard source (R7, currently 4.7 k with no filter capacitor).
- [ ] Resume the touch-proof jack board, with the input protection resistors on it.
- [ ] Add the missing revisions listed above from your drive.

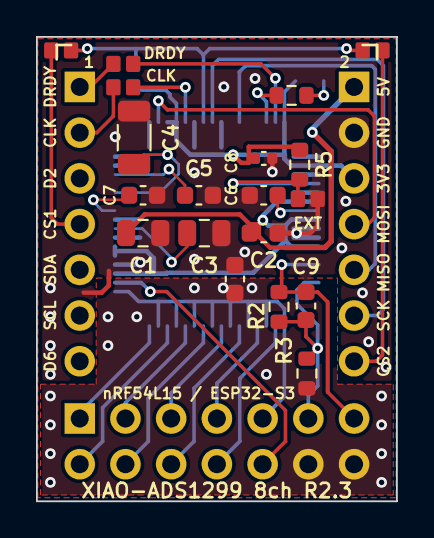
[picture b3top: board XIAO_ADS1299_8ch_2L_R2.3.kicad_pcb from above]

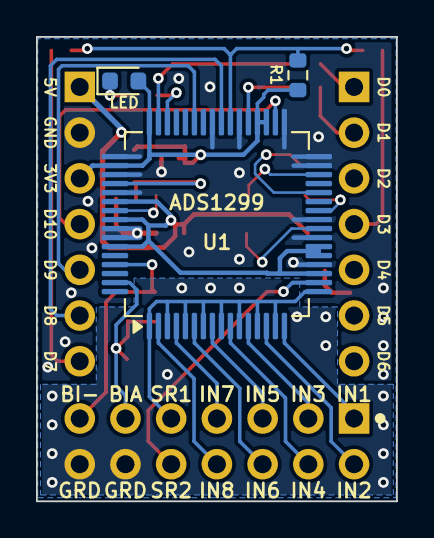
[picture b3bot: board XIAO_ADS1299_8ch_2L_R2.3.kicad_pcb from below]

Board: 2 copper layers, 20.0 x 25.8 mm, 25 parts (4 on the bottom side), 34 nets.

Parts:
C1, C3: 10u; C_0805_2012Metric
C2, C5, C6, C7: 1u; C_0603_1608Metric
C4: 100u; C_1206_3216Metric
C8: 1u X5R 0402; C_0402_1005Metric
C9: 1.5n C0G; C_0603_1608Metric
C10: 2.2u X7R; C_0603_1608Metric
D1: LED; LED_0603_1608Metric
J1: XIAO D0-D6; PinHeader_1x07_P2.54mm_Vertical
J2: XIAO 5V..D7; PinHeader_1x07_P2.54mm_Vertical
J3: Out 2x7 RA; PinHeader_2x07_P2.54mm_Horizontal
JP1: CS to D3; SJ2
JP2: CLK to D4; SJ2
JP3: CLKSEL to GND (ext clock); SJ2
JP4: DRDY to D10; SJ2
JP5: CS to D7; SJ2
R1, R5: 10k; R_0603_1608Metric
R2: 1M; R_0603_1608Metric
R3: 100k; R_0603_1608Metric
R4: 3.3k; R_0603_1608Metric
U1: ADS1299IPAG; TQFP-64_10x10mm_P0.5mm

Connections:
AVDD: C1.1, C2.1, J2.1, U1.19, U1.21, U1.22, U1.54, U1.56, U1.59
BIASINV: C9.1, J3.13, R2.1, U1.61
BIASOUT: C9.2, J3.11, R2.2, R3.1, U1.63
CLK: JP2.2, U1.37
CLKSEL: JP3.1, R5.1, U1.52
CS: JP1.1, JP5.1, R1.2, U1.39
DRDY: JP4.1, U1.47
DVDD: C8.1, D1.2, J2.3, R1.1, R5.2, U1.35, U1.36, U1.48, U1.50
GND: C1.2, C2.2, C3.2, C4.2, C5.2, C6.2, C7.2, C8.2, C10.1, J2.2, JP3.2, U1.20, U1.23, U1.25, U1.31, U1.32, U1.33, U1.38, U1.41, U1.49, U1.51, U1.53, U1.57, U1.58
GPIO4: R4.1, U1.46
GUARD: C10.2, J3.12, J3.14, R3.2
IN1P: J3.1, U1.16
IN2P: J3.2, U1.14
IN3P: J3.3, U1.12
IN4P: J3.4, U1.10
IN5P: J3.5, U1.8
IN6P: J3.6, U1.6
IN7P: J3.7, U1.4
IN8P: J3.8, U1.2
LED_K: D1.1, R4.2
MISO: J2.5, U1.43
MOSI: J2.4, U1.34
SCK: J2.6, U1.40
SRB1: J3.9, U1.1, U1.3, U1.5, U1.7, U1.9, U1.11, U1.13, U1.15, U1.17
SRB2: J3.10, U1.18
VCAP1: C4.1, U1.28
VCAP2: C5.1, U1.30
VCAP3: C6.1, U1.55
VCAP4: C7.1, U1.26
VREFP: C3.1, U1.24
XCLK: J1.2, JP2.1
XCS1: J1.4, JP1.2
XCS2: J2.7, JP5.2
XDRDY: J1.1, JP4.2

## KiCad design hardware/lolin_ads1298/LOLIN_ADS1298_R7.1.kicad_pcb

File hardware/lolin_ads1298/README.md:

# LOLIN ADS1298 board, 8 channels, R7.1 (18-pin flex inputs)

**R7.1** is the 18-pin flex board with every via moved off component pads. Earlier revisions: R7. Board-to-board pinouts, parts and placement are unchanged.

## R7.1 changes: vias off pads
A via on or touching a small pad can wick solder away from the joint. On 0.5 mm-pitch pins its ring can also bridge to the next pin.

- **New positions:** each via now sits beside its pad, joined by a short straight or 45° trace.
- **Re-joined traces:** traces that met the via are re-routed from their previous corner, straight and at 45°.
- **Checks:** the design-rule report matches the original board's line for line, nothing is unconnected, and `tools/check_via_in_pad.py` finds no via in any part pad.
- **"Drill clear" rows** in the table: the hole is off the pad and the ring still touches the pad edge. Vias are tented, so no solder reaches the hole.
- **U1 pin 62 (AVDD):** the via sits just past the pin tip with its drill clear. The ring still touches the tip, because neighbouring traces leave no room further out. Its top-side trace to the decoupling cap is rerouted at 45°, where it used to run at an angle.

| Pad | Net | Via moved | Distance | Result |
|---|---|---|---|---|
| U1.62 | AVDD | (17.55, 18.55) → (17.45, 18.55) | 0.10 mm | drill clear |
| C8.2 | GND | (15.50, 15.20) → (15.41, 15.44) | 0.25 mm | clear |
| D1.1 | GND | (8.30, 6.80) → (7.81, 7.14) | 0.60 mm | clear |
| C7.2 | GND | (15.10, 17.15) → (14.63, 17.32) | 0.50 mm | clear |
| JP6.1 | GND | (17.95, 8.30) → (17.66, 8.50) | 0.35 mm | clear |
| C4.2 | GND | (11.30, 13.60) → (9.95, 14.55) | 1.65 mm | clear |
| C3.2 | GND | (9.30, 16.40) → (9.05, 16.57) | 0.30 mm | clear |
| C6.1 | GND | (5.45, 24.05) → (5.19, 24.20) | 0.30 mm | clear |
| J1.17 | WCT | (8.45, 23.50) → (8.45, 23.45) | 0.05 mm | clear |

`plots/*_via_check.png` shows pads and vias, before and after.

## Inputs, aux header and guard
See [`../FLEX18.md`](../FLEX18.md): 18-pin Hirose FH12 flex input, 2×3 1.27 mm aux header, and closed guard on all four layers.

## Files
| File | Contents |
|---|---|
| `LOLIN_ADS1298_R7.1.kicad_pcb` / `.kicad_pro` | KiCad 7 board and rules |
| `gerber/` | Gerbers and drill file (4 layers) |
| `LOLIN_ADS1298_R7.1_BOM.csv` | Bill of materials |
| `plots/` | Top/bottom view, copper by net, via check |

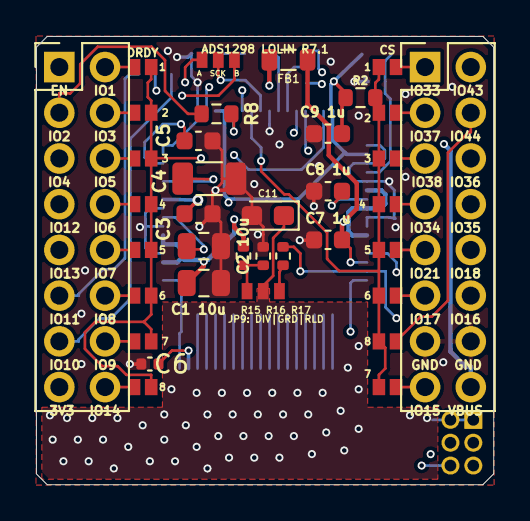
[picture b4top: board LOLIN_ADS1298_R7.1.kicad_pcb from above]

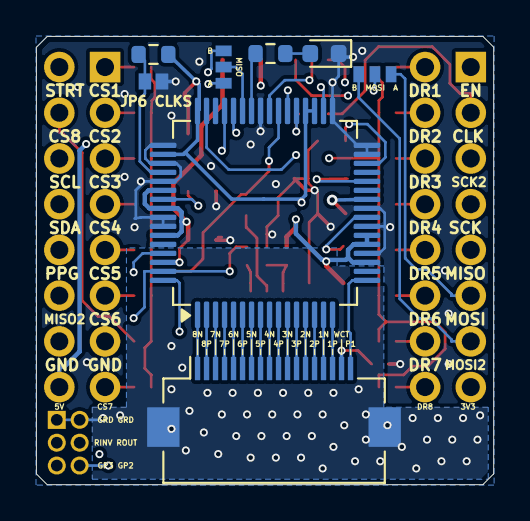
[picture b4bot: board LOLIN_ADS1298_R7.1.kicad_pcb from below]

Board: 4 copper layers, 25.4 x 24.9 mm, 45 parts (9 on the bottom side), 67 nets.

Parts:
C1: 10uF 25V; C_0805_2012Metric
C2: 10uF; C_0805_2012Metric
C3, C5, C7, C8, C9: 1uF; C_0603_1608Metric
C4: 22uF 6.3V; C_1206_3216Metric
C6: 100pF C0G; C_0402_1005Metric
C11: 4.7u 10V tant; CP_EIA-2012-12_Kemet-R
D1: LED 0603; LED_0603_1608Metric
FB1: Ferrite 600R@100MHz; L_0805_2012Metric
J1: FH12-18S-0.5SH(55); Hirose_FH12-18S-0.5SH_1x18-1MP_P0.50mm_Horizontal
J2: S3Mini_J2; PinHeader_2x08_P2.54mm_Vertical
J3: S3Mini_J3; PinHeader_2x08_P2.54mm_Vertical
J4: 2x3 1.27mm; PinHeader_2x03_P1.27mm_Vertical
JP6: CLKS
JP9: GUARD SRC: DIV|BIAS; SolderJumper_3_small
JP11: CS1
JP12: CS2
JP13: CS3
JP14: CS4
JP15: CS5
JP16: CS6
JP17: CS8
JP18: CS7
JP21: DRDY1
JP22: DRDY2
JP23: DRDY3
JP24: DRDY4
JP25: DRDY5
JP26: DRDY6
JP27: DRDY7
JP28: DRDY8
JP31: SCLK: A|B; SolderJumper_3_small
JP32: DOUT: A|B; SolderJumper_3_small
JP33: DIN: A|B; SolderJumper_3_small
R2, R4: 10k; R_0603_1608Metric
R8: 100R; R_0603_1608Metric
R9: 3.3k; R_0603_1608Metric
R15, R16: 200k; R_0402_1005Metric
R17: 4.7k (RLD); R_0402_1005Metric
U1: ADS1298IPAG; TQFP-64_10x10mm_P0.5mm

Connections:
+5V: FB1.1, J3.16
AVDD: C1.1, C7.1, FB1.2, R15.1, U1.19, U1.21, U1.22, U1.54, U1.56, U1.59, U1.62
CLK: R8.2, U1.37
CLKSEL: JP6.2, R4.2, U1.52
CLK_BUS: J2.3, R8.1
CS1: J3.1, JP11.2
CS2: J3.3, JP12.2
CS3: J3.5, JP13.2
CS4: J3.7, JP14.2
CS5: J3.9, JP15.2
CS6: J3.11, JP16.2
CS7: J3.15, JP18.2
CS8: J3.4, JP17.2
CS_LOCAL: JP11.1, JP12.1, JP13.1, JP14.1, JP15.1, JP16.1, JP17.1, JP18.1, R2.2, U1.39
DIN: JP33.2, U1.34
DOUT: JP32.2, U1.43
DRDY1: J2.2, JP21.1
DRDY2: J2.4, JP22.1
DRDY3: J2.6, JP23.1
DRDY4: J2.8, JP24.1
DRDY5: J2.10, JP25.1
DRDY6: J2.12, JP26.1
DRDY7: J2.14, JP27.1
DRDY8: J2.16, JP28.1
DRDY_LOCAL: JP21.2, JP22.2, JP23.2, JP24.2, JP25.2, JP26.2, JP27.2, JP28.2, U1.47
DVDD: C9.1, J2.15, R2.1, R4.1, U1.35, U1.36, U1.48, U1.50
GBIAS: JP9.3, R17.1
GDIV: JP9.1, R15.2, R16.1
GND: C1.2, C2.2, C3.2, C4.2, C5.2, C6.1, C7.2, C8.2, C9.2, C11.2, D1.1, J3.13, J3.14, JP6.1, R16.2, U1.20, U1.23, U1.25, U1.31, U1.32, U1.33, U1.41, U1.49, U1.51, U1.53, U1.57, U1.58
GPIO1: R9.2, U1.42
GPIO2: J4.6, U1.44
GPIO3: J4.5, U1.45
GUARD: C11.1, J1.MP, J4.1, J4.2, JP9.2
IN1N: J1.15, U1.15
IN1P: J1.16, U1.16
IN2N: J1.13, U1.13
IN2P: J1.14, U1.14
IN3N: J1.11, U1.11
IN3P: J1.12, U1.12
IN4N: J1.9, U1.9
IN4P: J1.10, U1.10
IN5N: J1.7, U1.7
IN5P: J1.8, U1.8
IN6N: J1.5, U1.5
IN6P: J1.6, U1.6
IN7N: J1.3, U1.3
IN7P: J1.4, U1.4
IN8N: J1.1, U1.1
IN8P: J1.2, U1.2
LED_A: D1.2, R9.1
MISO: J2.9, JP32.1
MISO2: J3.12, JP32.3
MOSI: J2.11, JP33.1
MOSI2: J2.13, JP33.3
PACE1: J1.18, U1.17
RLDINV: J4.3, U1.61
RLDOUT: J4.4, R17.2, U1.63
SCK: J2.7, JP31.1
SCK2: J2.5, JP31.3
SCLK: JP31.2, U1.40
START: J3.2, U1.38
VCAP1: C4.1, U1.28
VCAP2: C5.1, U1.30
VCAP3: C8.1, U1.55
VCAP4: C3.1, U1.26
VREFP: C2.1, U1.24
WCT: C6.2, J1.17, U1.64

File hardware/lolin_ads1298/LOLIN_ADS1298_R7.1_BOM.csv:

Refs,Qty,Value / part,Footprint,Side
C1,1,10uF 25V,C_0805_2012Metric,Top
C2,1,10uF,C_0805_2012Metric,Top
C3 C5 C7 C8 C9,5,1uF,C_0603_1608Metric,Top
C4,1,22uF 6.3V,C_1206_3216Metric,Top
C6,1,100pF C0G,C_0402_1005Metric,Top
C11,1,4.7u 10V tant,CP_EIA-2012-12_Kemet-R,Top
D1,1,LED 0603,LED_0603_1608Metric,Bottom
FB1,1,Ferrite 600R@100MHz,L_0805_2012Metric,Top
J1,1,FH12-18S-0.5SH(55),Hirose_FH12-18S-0.5SH_1x18-1MP_P0.50mm_Horizontal,Bottom
J2,1,S3Mini_J2,PinHeader_2x08_P2.54mm_Vertical,Top
J3,1,S3Mini_J3,PinHeader_2x08_P2.54mm_Vertical,Top
J4,1,2x3 1.27mm,PinHeader_2x03_P1.27mm_Vertical,Bottom
R2,1,10k,R_0603_1608Metric,Top
R4,1,10k,R_0603_1608Metric,Bottom
R8,1,100R,R_0603_1608Metric,Top
R9,1,3.3k,R_0603_1608Metric,Bottom
R15 R16,2,200k,R_0402_1005Metric,Top
R17,1,4.7k (RLD),R_0402_1005Metric,Top
U1,1,ADS1298IPAG,TQFP-64_10x10mm_P0.5mm,Bottom

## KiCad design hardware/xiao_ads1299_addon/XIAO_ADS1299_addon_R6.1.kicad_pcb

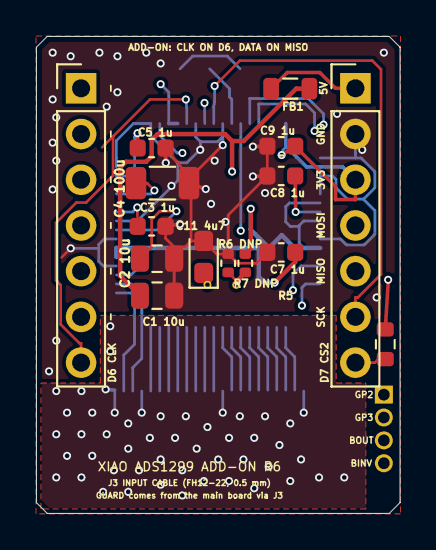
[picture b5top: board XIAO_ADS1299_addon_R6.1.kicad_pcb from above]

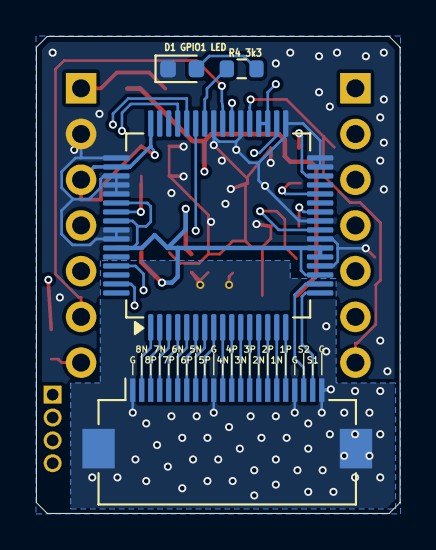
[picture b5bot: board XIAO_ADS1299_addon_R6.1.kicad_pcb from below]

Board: 4 copper layers, 20.2 x 26.5 mm, 22 parts (5 on the bottom side), 39 nets.

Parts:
C1, C2: 10u; C_0805_2012Metric
C3, C5, C7, C8, C9: 1u; C_0603_1608Metric
C4: 100u; C_1206_3216Metric
C11: 4.7u 10V tant; CP_EIA-2012-12_Kemet-R
D1: LED; LED_0603_1608Metric
FB1: 600R@100MHz; L_0805_2012Metric
GV1, GV2: guard via; GuardVia
J1: XIAO left (pass-through); PinHeader_1x07_P2.54mm_Vertical
J2: XIAO right (pass-through); PinHeader_1x07_P2.54mm_Vertical
J3: FH12-22S-0.5SH(55); Hirose_FH12-22S-0.5SH_1x22-1MP_P0.50mm_Horizontal
J4: 1x4 1.27mm; PinHeader_1x04_P1.27mm_Vertical
R4: 3.3k; R_0603_1608Metric
R5: 10k; R_0603_1608Metric
R6, R7: 200k; R_0402_1005Metric
U1: ADS1299IPAG (or -6 / -4); TQFP-64_10x10mm_P0.5mm

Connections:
+5V: FB1.1, J2.1
AVDD: C1.1, C7.1, FB1.2, R6.2, U1.19, U1.21, U1.22, U1.54, U1.56, U1.59
BIASINV: J4.4, U1.61
BIASOUT: J4.3, U1.63
CLK: J1.7, U1.37
CS2: J2.7, R5.2, U1.39
DVDD: C9.1, J2.3, R5.1, U1.35, U1.36, U1.48, U1.50
GND: C1.2, C2.2, C3.2, C4.2, C5.2, C7.2, C8.2, C9.2, C11.2, D1.1, J2.2, R7.2, U1.20, U1.23, U1.25, U1.31, U1.32, U1.33, U1.38, U1.41, U1.49, U1.51, U1.52, U1.53, U1.57, U1.58
GPIO1: R4.1, U1.42
GPIO2: J4.1, U1.44
GPIO3: J4.2, U1.45
GUARD: C11.1, GV1.1, GV2.1, J3.1, J3.10, J3.19, J3.22, J3.MP, R6.1, R7.1
IN1N: J3.17, U1.15
IN1P: J3.18, U1.16
IN2N: J3.15, U1.13
IN2P: J3.16, U1.14
IN3N: J3.13, U1.11
IN3P: J3.14, U1.12
IN4N: J3.11, U1.9
IN4P: J3.12, U1.10
IN5N: J3.8, U1.7
IN5P: J3.9, U1.8
IN6N: J3.6, U1.5
IN6P: J3.7, U1.6
IN7N: J3.4, U1.3
IN7P: J3.5, U1.4
IN8N: J3.2, U1.1
IN8P: J3.3, U1.2
LED_A: D1.2, R4.2
MISO: J2.5, U1.43
MOSI: J2.4, U1.34
SCK: J2.6, U1.40
SRB1: J3.21, U1.17
SRB2: J3.20, U1.18
VCAP1: C4.1, U1.28
VCAP2: C5.1, U1.30
VCAP3: C8.1, U1.55
VCAP4: C3.1, U1.26
VREFP: C2.1, U1.24

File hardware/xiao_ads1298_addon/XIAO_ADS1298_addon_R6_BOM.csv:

Refs,Qty,Value / part,Footprint,Side
C1 C2,2,10u,C_0805_2012Metric,Top
C3 C5 C7 C8 C9,5,1u,C_0603_1608Metric,Top
C4,1,22uF 6.3V,C_1206_3216Metric,Top
C11,1,4.7u 10V tant,CP_EIA-2012-12_Kemet-R,Top
D1,1,LED,LED_0603_1608Metric,Bottom
FB1,1,600R@100MHz,L_0805_2012Metric,Top
J1,1,XIAO left (pass-through),PinHeader_1x07_P2.54mm_Vertical,Top
J2,1,XIAO right (pass-through),PinHeader_1x07_P2.54mm_Vertical,Top
J3,1,FH12-22S-0.5SH(55),Hirose_FH12-22S-0.5SH_1x22-1MP_P0.50mm_Horizontal,Bottom
J4,1,1x4 1.27mm,PinHeader_1x04_P1.27mm_Vertical,Bottom
R4,1,3.3k,R_0603_1608Metric,Bottom
R5,1,10k,R_0603_1608Metric,Top
R6 R7,2,200k,R_0402_1005Metric,Top
U1,1,ADS1298IPAG,TQFP-64_10x10mm_P0.5mm,Bottom
